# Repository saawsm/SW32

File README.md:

# SW32 - 4 Channel E-Stim

*This project is a work in-progress. Changes to the design might occur. Order PCBs at your own risk..*

---

## About

The SW32 is a 4-channel E-Stim box based around the MK312 box. Focusing on a modern and compact redesign. It supports USB Type-C PD charging with a variety of batteries such as Li-Ion, Li-Poly, or Lead Acid.

Controlling and interacting with the box can be achieved in numerous ways. Such as the front panel controls, USB, Bluetooth/A2DP, or via Wi-Fi using the internally hosted web app.

An RP2040 microcontroller was picked since it has dual cores and the [PIO](https://www.raspberrypi.com/documentation/pico-sdk/hardware.html#rpip27a2111bf36b4a04eb7b) hardware peripheral. An active community and well documented SDK is also a bonus.

## Features

* 1.8" 160x128 Color Display
* 4x Isolated Output Channels
  * Triphase Support
  * Tri-polar (+, GND, -) Support
* Stereo Line-In and Mono Microphone Input (with programmable gain)
* Internal Microphone
* 4x Trigger Channels
* USB Type-C PD Charging
* Multi-chemistry Battery Pack Support (Li-Ion/Li-Poly/Lead Acid)

## Overview

The SW32 consists of following PCBs:

* Main Board - Provides the core functionality of the SW32.
* Output Board - Generates the isolated E-Stim output for each channel. Driven by the main board.
* Front Control Board - The PCB with all the front panel controls (e.g. pots, buttons, LEDs).
* Front Panel - A cosmetic silkscreen PCB for the front control board.
* Display Module* - 1.8" 160x128 TFT SPI color display.

The reason for having a separate output board is primarily for flexibility, space savings (expand vertically instead of horizontally), and long-term cost savings. Most of the cost is in the main board. So being able to reuse the main board when changing the output design will help keep costs down.

## Fabrication

This build is mostly SMT with THT for connectors and front panel components. PCBs have been designed specifically for JLCPCB fabrication and assembly.

Schematics can be found in [/schematics](/schematics), and PCB fabrication files (gerbers, BoMs, CPL, etc.) can be found in [/pcb](/pcb).

## Disclaimer

The SW32 comes with absolutely no warranty of any kind. The designs are free to use, under the conditions defined in the [LICENSE](LICENSE). Using the designs in original or modified form, implies acceptance of any and all associated risks and liabilities.

* Use it entirely at your own risk.
* Do not use it for anything safety-critical, medical, industrial, military, or illegal.
* Do not use it on anyone without explicit and informed consent.
* Keep any and all electrodes below the chest.
* Do not use Li-Ion battery packs without a BMS.

### Safety

SW32 can generate potentially lethal voltages and currents on its outputs and on internal components, even when powered from a battery. The risks associated with building, testing and using this device can be reduced but not eliminated.

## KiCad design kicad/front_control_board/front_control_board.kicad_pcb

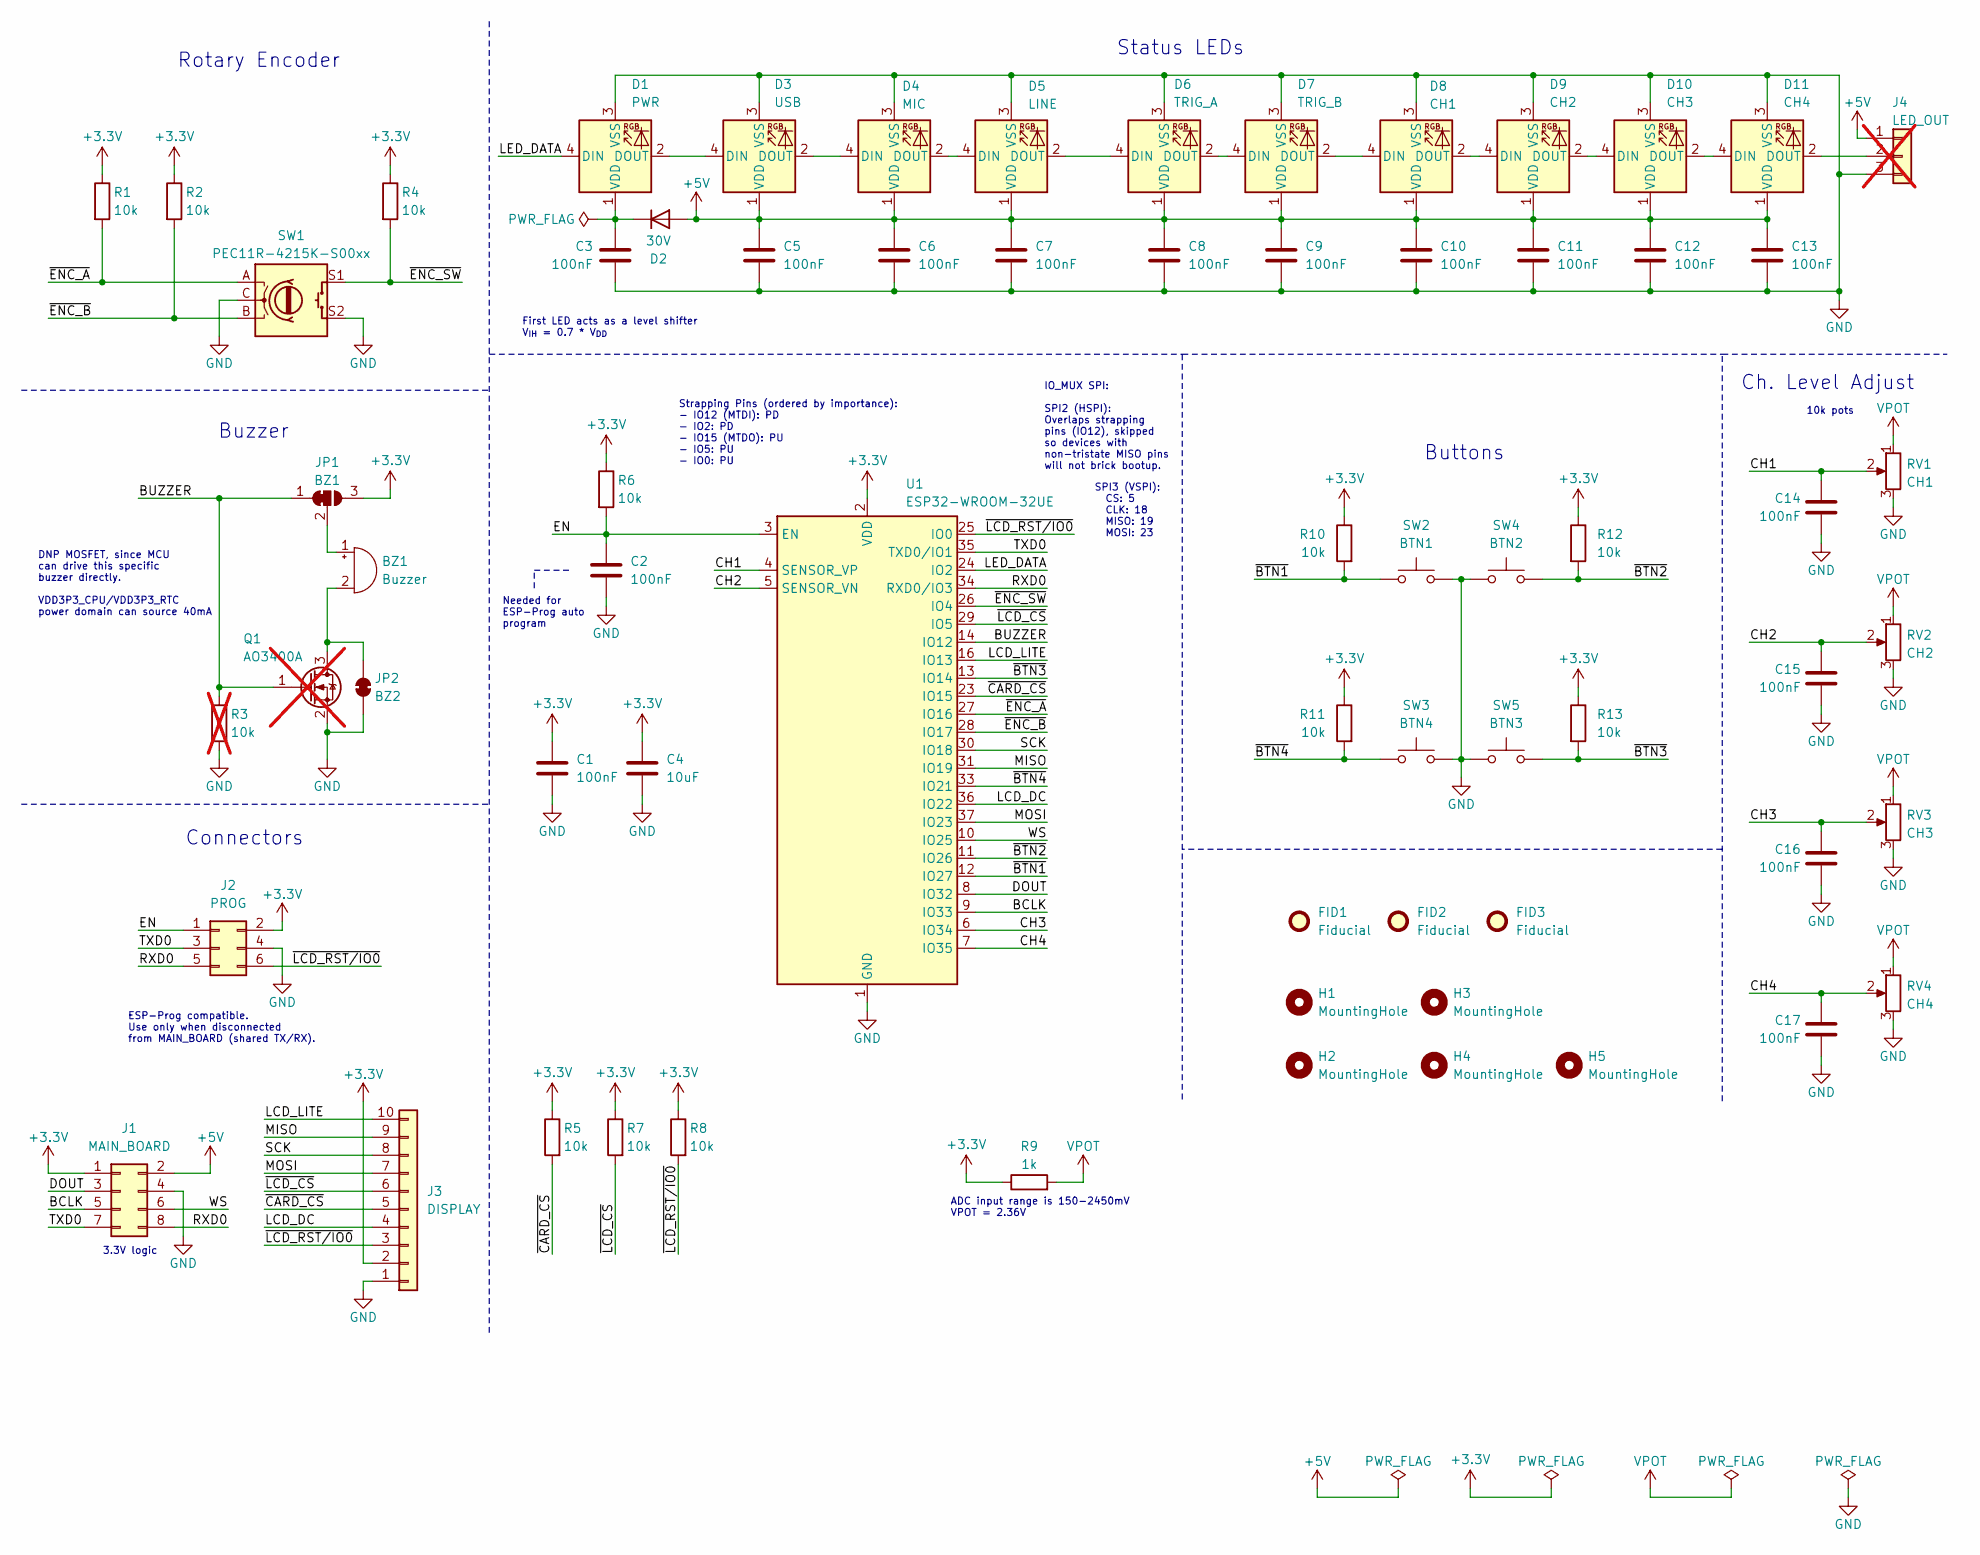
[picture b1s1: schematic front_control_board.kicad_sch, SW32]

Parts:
BZ1: Buzzer; Buzzer_12x9.5RM7.6; LCSC C409834
C1, C2, C3, C5, C6, C7, C8, C9, C10, C11, C12, C13, C14, C15, C16, C17: 100nF; C_0603_1608Metric; LCSC C14663
C4: 10uF; C_0603_1608Metric; LCSC C96446
D1: PWR; LED_WS2812B_PLCC4_5.0x5.0mm_P3.2mm; LCSC C2843785
D2: 30V; D_SOD-323; LCSC C2128
D3: USB; LED_WS2812B_PLCC4_5.0x5.0mm_P3.2mm; LCSC C2843785
D4: MIC; LED_WS2812B_PLCC4_5.0x5.0mm_P3.2mm; LCSC C2843785
D5: LINE; LED_WS2812B_PLCC4_5.0x5.0mm_P3.2mm; LCSC C2843785
D6: TRIG_A; LED_WS2812B_PLCC4_5.0x5.0mm_P3.2mm; LCSC C2843785
D7: TRIG_B; LED_WS2812B_PLCC4_5.0x5.0mm_P3.2mm; LCSC C2843785
D8: CH1; LED_WS2812B_PLCC4_5.0x5.0mm_P3.2mm; LCSC C2843785
D9: CH2; LED_WS2812B_PLCC4_5.0x5.0mm_P3.2mm; LCSC C2843785
D10: CH3; LED_WS2812B_PLCC4_5.0x5.0mm_P3.2mm; LCSC C2843785
D11: CH4; LED_WS2812B_PLCC4_5.0x5.0mm_P3.2mm; LCSC C2843785
FID1, FID2, FID3: Fiducial; Fiducial_1mm_Mask2mm
H1, H2, H3, H4, H5: MountingHole; MountingHole_2.2mm_M2
J1: MAIN_BOARD; IDC-Header_2x04_P2.54mm_Vertical; LCSC C5372864
J2: PROG; IDC-Header_2x03_P2.54mm_Vertical; LCSC C5372863
J3: DISPLAY; PinHeader_1x10_P2.54mm_Vertical; LCSC C492409
J4: LED_OUT; PinHeader_1x03_P2.54mm_Vertical; LCSC C2937625; not fitted
JP1: BZ1; SolderJumper-3_P1.3mm_Bridged12_RoundedPad1.0x1.5mm_NumberL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
JP2: BZ2; SolderJumper-2_P1.3mm_Bridged_RoundedPad1.0x1.5mm
Q1: AO3400A; SOT-23; LCSC C20917; not fitted
R1, R2, R4, R5, R6, R7, R8, R10, R11, R12, R13: 10k; R_0603_1608Metric; LCSC C25804
R3: 10k; R_0603_1608Metric; LCSC C25804; not fitted
R9: 1k; R_0603_1608Metric; LCSC C21190
RV1: CH1; Potentiometer_Bourns_PTV09A-1_Single_Vertical; LCSC C6149573
RV2: CH2; Potentiometer_Bourns_PTV09A-1_Single_Vertical; LCSC C6149573
RV3: CH3; Potentiometer_Bourns_PTV09A-1_Single_Vertical; LCSC C6149573
RV4: CH4; Potentiometer_Bourns_PTV09A-1_Single_Vertical; LCSC C6149573
SW1: PEC11R-4215K-S00xx; Rotary_Encoder_Switched_PEC11R; LCSC C7275025
SW2: BTN1; SW_PUSH_6mm_H5mm; LCSC C393938
SW3: BTN4; SW_PUSH_6mm_H5mm; LCSC C393938
SW4: BTN2; SW_PUSH_6mm_H5mm; LCSC C393938
SW5: BTN3; SW_PUSH_6mm_H5mm; LCSC C393938
U1: ESP32-WROOM-32UE; LCSC C701346

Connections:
+3.3V: C1.1, C4.1, J1.1, J2.2, J3.2, JP1.3 (B), R1.1, R2.1, R4.1, R5.1, R6.1, R7.1, R8.1, R9.1, R10.1, R11.1, R12.1, R13.1, U1.2 (VDD)
+5V: C5.1, C6.1, C7.1, C8.1, C9.1, C10.1, C11.1, C12.1, C13.1, D2.2 (A), D3.1 (VDD), D4.1 (VDD), D5.1 (VDD), D6.1 (VDD), D7.1 (VDD), D8.1 (VDD), D9.1 (VDD), D10.1 (VDD), D11.1 (VDD), J1.2, J4.1
/BCLK: J1.5, U1.9 (IO33)
/BUZZER: JP1.1 (A), Q1.1 (G), R3.2, U1.14 (IO12)
/CH1: C14.1, RV1.2, U1.4 (SENSOR_VP)
/CH2: C15.1, RV2.2, U1.5 (SENSOR_VN)
/CH3: C16.1, RV3.2, U1.6 (IO34)
/CH4: C17.1, RV4.2, U1.7 (IO35)
/DOUT: J1.3, U1.8 (IO32)
/EN: C2.1, J2.1, R6.2, U1.3 (EN)
/LCD_DC: J3.4, U1.36 (IO22)
/LCD_LITE: J3.10, U1.16 (IO13)
/LED_DATA: D1.4 (DIN), U1.24 (IO2)
/MISO: J3.9, U1.31 (IO19)
/MOSI: J3.7, U1.37 (IO23)
/RXD0: J1.8, J2.5, U1.34 (RXD0/IO3)
/SCK: J3.8, U1.30 (IO18)
/TXD0: J1.7, J2.3, U1.35 (TXD0/IO1)
/WS: J1.6, U1.10 (IO25)
/~BTN1: R10.2, SW2.2, U1.12 (IO27)
/~BTN2: R12.2, SW4.2, U1.11 (IO26)
/~BTN3: R13.2, SW5.2, U1.13 (IO14)
/~BTN4: R11.2, SW3.2, U1.33 (IO21)
/~CARD_CS: J3.5, R5.2, U1.23 (IO15)
/~ENC_A: R1.2, SW1.A, U1.27 (IO16)
/~ENC_B: R2.2, SW1.B, U1.28 (IO17)
/~ENC_SW: R4.2, SW1.S1, U1.26 (IO4)
/~LCD_CS: J3.6, R7.2, U1.29 (IO5)
/~LCD_RST/IO0: J2.6, J3.3, R8.2, U1.25 (IO0)
GND: C1.2, C2.2, C3.2, C4.2, C5.2, C6.2, C7.2, C8.2, C9.2, C10.2, C11.2, C12.2, C13.2, C14.2, C15.2, C16.2, C17.2, D1.3 (VSS), D3.3 (VSS), D4.3 (VSS), D5.3 (VSS), D6.3 (VSS), D7.3 (VSS), D8.3 (VSS), D9.3 (VSS), D10.3 (VSS), D11.3 (VSS), J1.4, J2.4, J3.1, J4.3, JP2.1 (A), Q1.2 (S), R3.1, RV1.3, RV2.3, RV3.3, RV4.3, SW1.C, SW1.S2, SW2.1, SW3.1, SW4.1, SW5.1, U1.1 (GND), U1.15 (GND), U1.38 (GND), U1.39 (GND)
unnamed: BZ1.1 (+), JP1.2 (C)
unnamed: BZ1.2 (-), JP2.2 (B), Q1.3 (D)
unnamed: D1.2 (DOUT), D3.4 (DIN)
unnamed: C3.1, D1.1 (VDD), D2.1 (K)
unnamed: D3.2 (DOUT), D4.4 (DIN)
unnamed: D4.2 (DOUT), D5.4 (DIN)
unnamed: D5.2 (DOUT), D6.4 (DIN)
unnamed: D6.2 (DOUT), D7.4 (DIN)
unnamed: D7.2 (DOUT), D8.4 (DIN)
unnamed: D8.2 (DOUT), D9.4 (DIN)
unnamed: D9.2 (DOUT), D10.4 (DIN)
unnamed: D10.2 (DOUT), D11.4 (DIN)
unnamed: D11.2 (DOUT), J4.2
VPOT: R9.2, RV1.1, RV2.1, RV3.1, RV4.1

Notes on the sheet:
Status LEDs
ADC input range is 150-2450mV VPOT = 2.36V
First LED acts as a level shifter V_{IH} = 0.7 * V_{DD}
Rotary Encoder
IO_MUX SPI: SPI2 (HSPI): Overlaps strapping pins (IO12), skipped so devices with non-tristate MISO pins will not brick bootup.
SPI3 (VSPI): CS: 5 CLK: 18 MISO: 19 MOSI: 23
Buttons
3.3V logic
ESP-Prog compatible. Use only when disconnected from MAIN_BOARD (shared TX/RX).
Strapping Pins (ordered by importance): - IO12 (MTDI): PD - IO2: PD - IO15 (MTDO): PU - IO5: PU - IO0: PU
Connectors
10k pots
Needed for ESP-Prog auto program
Buzzer
DNP MOSFET, since MCU can drive this specific buzzer directly. VDD3P3_CPU/VDD3P3_RTC power domain can source 40mA
Ch. Level Adjust

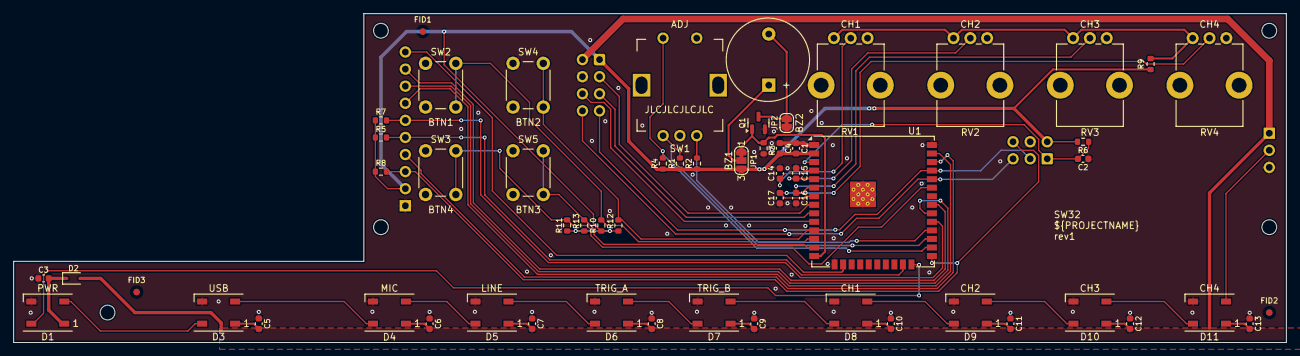
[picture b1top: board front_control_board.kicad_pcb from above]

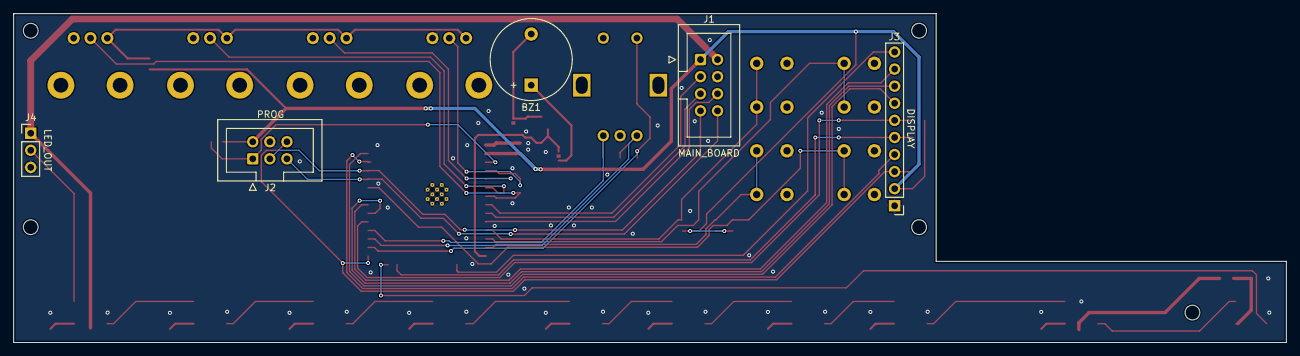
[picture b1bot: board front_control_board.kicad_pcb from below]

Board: 2 copper layers, 189.2 x 48.9 mm, 67 parts (5 on the bottom side), 44 nets.

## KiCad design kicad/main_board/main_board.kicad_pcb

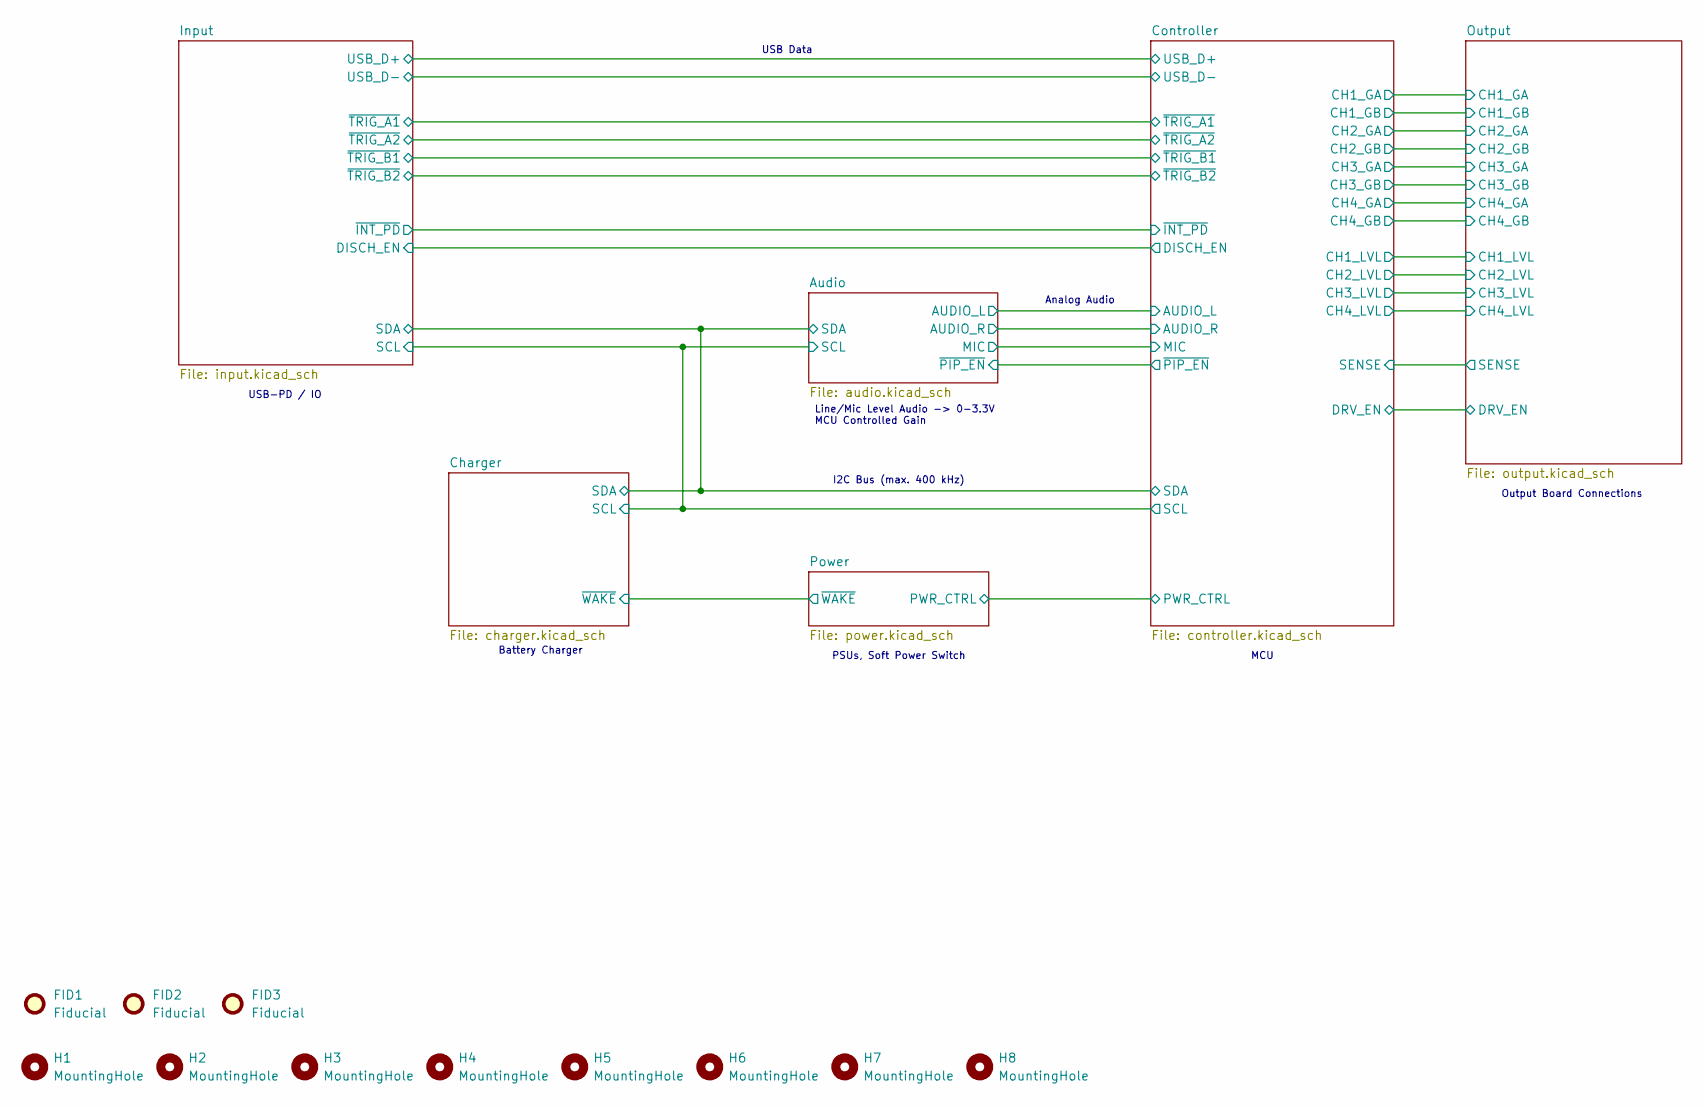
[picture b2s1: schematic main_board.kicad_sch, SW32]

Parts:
FID1, FID2, FID3: Fiducial; Fiducial_1mm_Mask2mm
H1, H2, H3, H4, H5, H6, H7, H8: MountingHole; MountingHole_2.2mm_M2

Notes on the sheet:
Output Board Connections
USB-PD / IO
MCU
USB Data
PSUs, Soft Power Switch
Line/Mic Level Audio -> 0-3.3V MCU Controlled Gain
Analog Audio
Battery Charger
I2C Bus (max. 400 kHz)

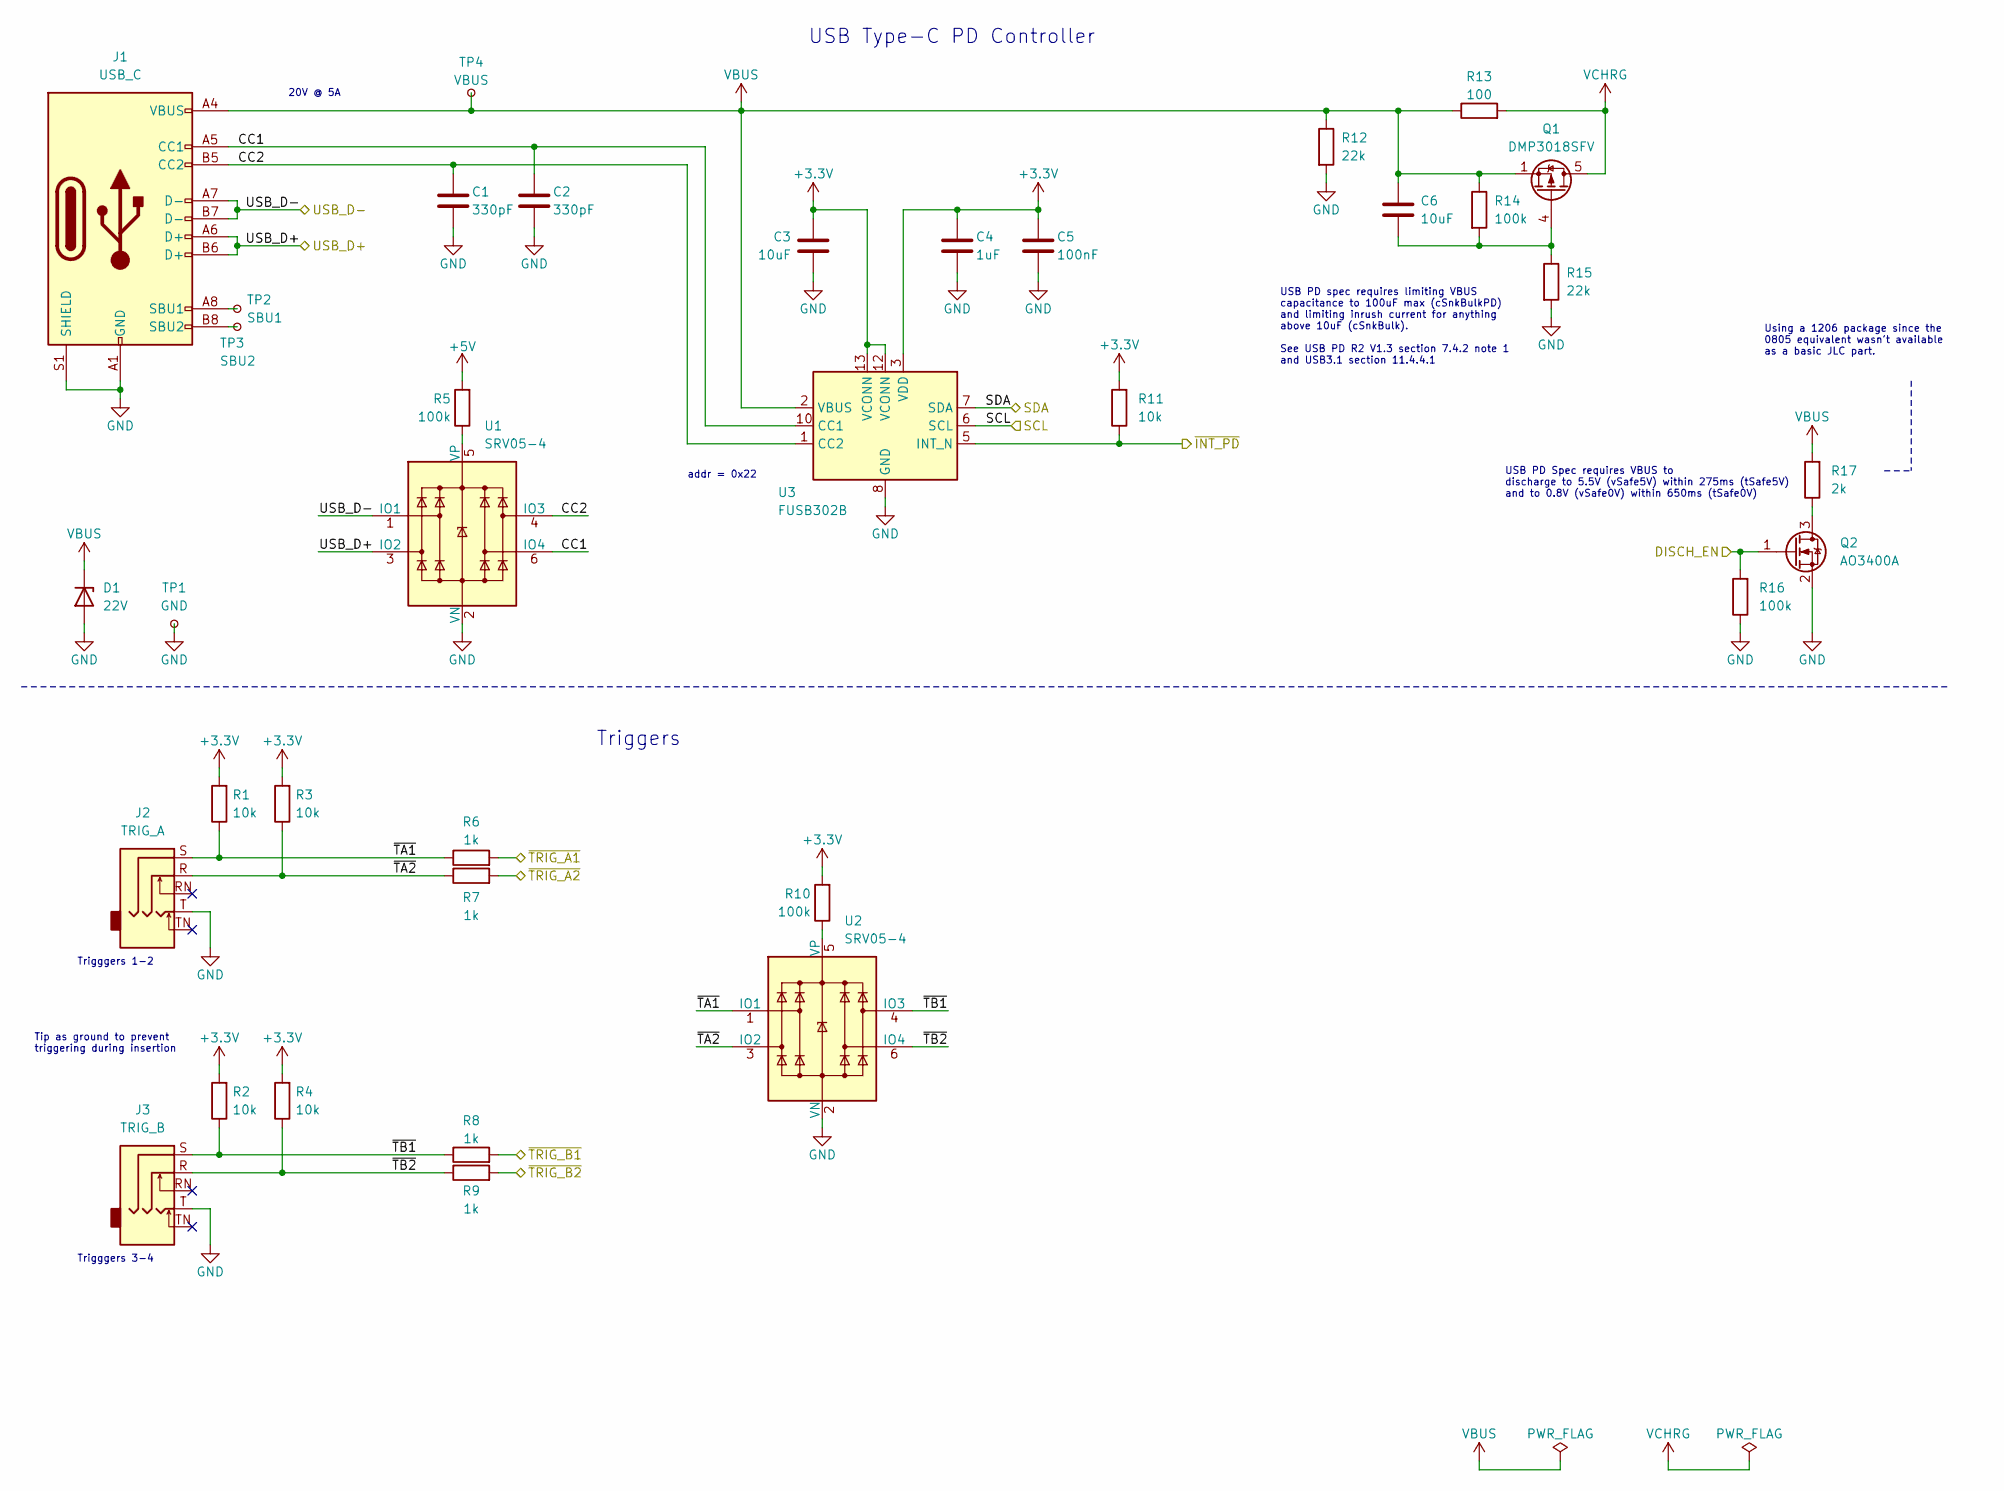
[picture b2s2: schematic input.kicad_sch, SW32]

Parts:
C1, C2: 330pF; C_0603_1608Metric; LCSC C1664
C3, C6: 10uF; C_0603_1608Metric; LCSC C96446
C4: 1uF; C_0603_1608Metric; LCSC C15849
C5: 100nF; C_0603_1608Metric; LCSC C14663
D1: 22V; ST_QFN-2L_1.6x1.0mm; LCSC C1974707
J1: USB_C; USB_C_Receptacle_GCT_USB4105-xx-A_16P_TopMnt_Horizontal; LCSC C2765186
J2: TRIG_A; PJ-3062-CO; LCSC C319113
J3: TRIG_B; PJ-3062-CO; LCSC C319113
Q1: DMP3018SFV; Diodes_PowerDI3333-8_ThermalVias; LCSC C461075
Q2: AO3400A; SOT-23; LCSC C20917
R1, R2, R3, R4, R11: 10k; R_0603_1608Metric; LCSC C25804
R5, R10, R14, R16: 100k; R_0603_1608Metric; LCSC C25803
R6, R7, R8, R9: 1k; R_0603_1608Metric; LCSC C21190
R12, R15: 22k; R_0603_1608Metric; LCSC C31850
R13: 100; R_1206_3216Metric; LCSC C17901
R17: 2k; R_1206_3216Metric; LCSC C17944
TP1: GND; TestPoint_Pad_D1.0mm
TP2: SBU1; TestPoint_Pad_D1.0mm
TP3: SBU2; TestPoint_Pad_D1.0mm
TP4: VBUS; TestPoint_Pad_D1.0mm
U1, U2: SRV05-4; SOT-23-6; LCSC C111212
U3: FUSB302B; WQFN-14-1EP_2.5x2.5mm_P0.5mm_EP1.45x1.45mm; LCSC C132291

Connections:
+3.3V: C3.1, C4.1, C5.1, R1.2, R2.2, R3.2, R4.2, R10.2, R11.2, U3.3 (VDD), U3.4 (VDD), U3.12 (VCONN), U3.13 (VCONN); also elsewhere on the board
+5V: R5.2; also elsewhere on the board
/Charger/SCL: U3.6 (SCL); also elsewhere on the board
/Charger/SDA: U3.7 (SDA); also elsewhere on the board
/Controller/DISCH_EN: Q2.1 (G), R16.2; also elsewhere on the board
/Controller/~INT_PD: R11.1, U3.5 (INT_N); also elsewhere on the board
/Controller/~TRIG_A1: R6.2; also elsewhere on the board
/Controller/~TRIG_A2: R7.2; also elsewhere on the board
/Controller/~TRIG_B1: R8.2; also elsewhere on the board
/Controller/~TRIG_B2: R9.2; also elsewhere on the board
/Input/CC1: C2.1, J1.A5 (CC1), U1.6 (IO4), U3.10 (CC1), U3.11 (CC1)
/Input/CC2: C1.1, J1.B5 (CC2), U1.4 (IO3), U3.1 (CC2), U3.14 (CC2)
/Input/USB_D+: J1.A6 (D+), J1.B6 (D+), U1.3 (IO2); also elsewhere on the board
/Input/USB_D-: J1.A7 (D-), J1.B7 (D-), U1.1 (IO1); also elsewhere on the board
/Input/~TA1: J2.S, R1.1, R6.1, U2.1 (IO1)
/Input/~TA2: J2.R, R3.1, R7.1, U2.3 (IO2)
/Input/~TB1: J3.S, R2.1, R8.1, U2.4 (IO3)
/Input/~TB2: J3.R, R4.1, R9.1, U2.6 (IO4)
GND: C1.2, C2.2, C3.2, C4.2, C5.2, D1.2 (A), J1.A1 (GND), J1.A12 (GND), J1.B1 (GND), J1.B12 (GND), J1.S1 (SHIELD), J2.T, J3.T, Q2.2 (S), R12.2, R15.2, R16.1, TP1.1, U1.2 (VN), U2.2 (VN), U3.8 (GND), U3.9 (GND), U3.15 (GND); also elsewhere on the board
unnamed: J1.A8 (SBU1), TP2.1
unnamed: J1.B8 (SBU2), TP3.1
unnamed: C6.2, Q1.4 (G), R14.2, R15.1
unnamed: Q2.3 (D), R17.1
unnamed: R5.1, U1.5 (VP)
unnamed: R10.1, U2.5 (VP)
VBUS: C6.1, D1.1 (K), J1.A4 (VBUS), J1.A9 (VBUS), J1.B4 (VBUS), J1.B9 (VBUS), Q1.1 (S), Q1.2 (S), Q1.3 (S), R12.1, R13.1, R14.1, R17.2, TP4.1, U3.2 (VBUS); also elsewhere on the board
VCHRG: Q1.5 (D), R13.2; also elsewhere on the board

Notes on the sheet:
USB Type-C PD Controller
Triggers
Trigggers 3-4
20V @ 5A
USB PD spec requires limiting VBUS capacitance to 100uF max (cSnkBulkPD) and limiting inrush current for anything above 10uF (cSnkBulk). See USB PD R2 V1.3 section 7.4.2 note 1 and USB3.1 section 11.4.4.1
Tip as ground to prevent triggering during insertion
Using a 1206 package since the 0805 equivalent wasn't available as a basic JLC part.
USB PD Spec requires VBUS to discharge to 5.5V (vSafe5V) within 275ms (tSafe5V) and to 0.8V (vSafe0V) within 650ms (tSafe0V)
addr = 0x22
Trigggers 1-2

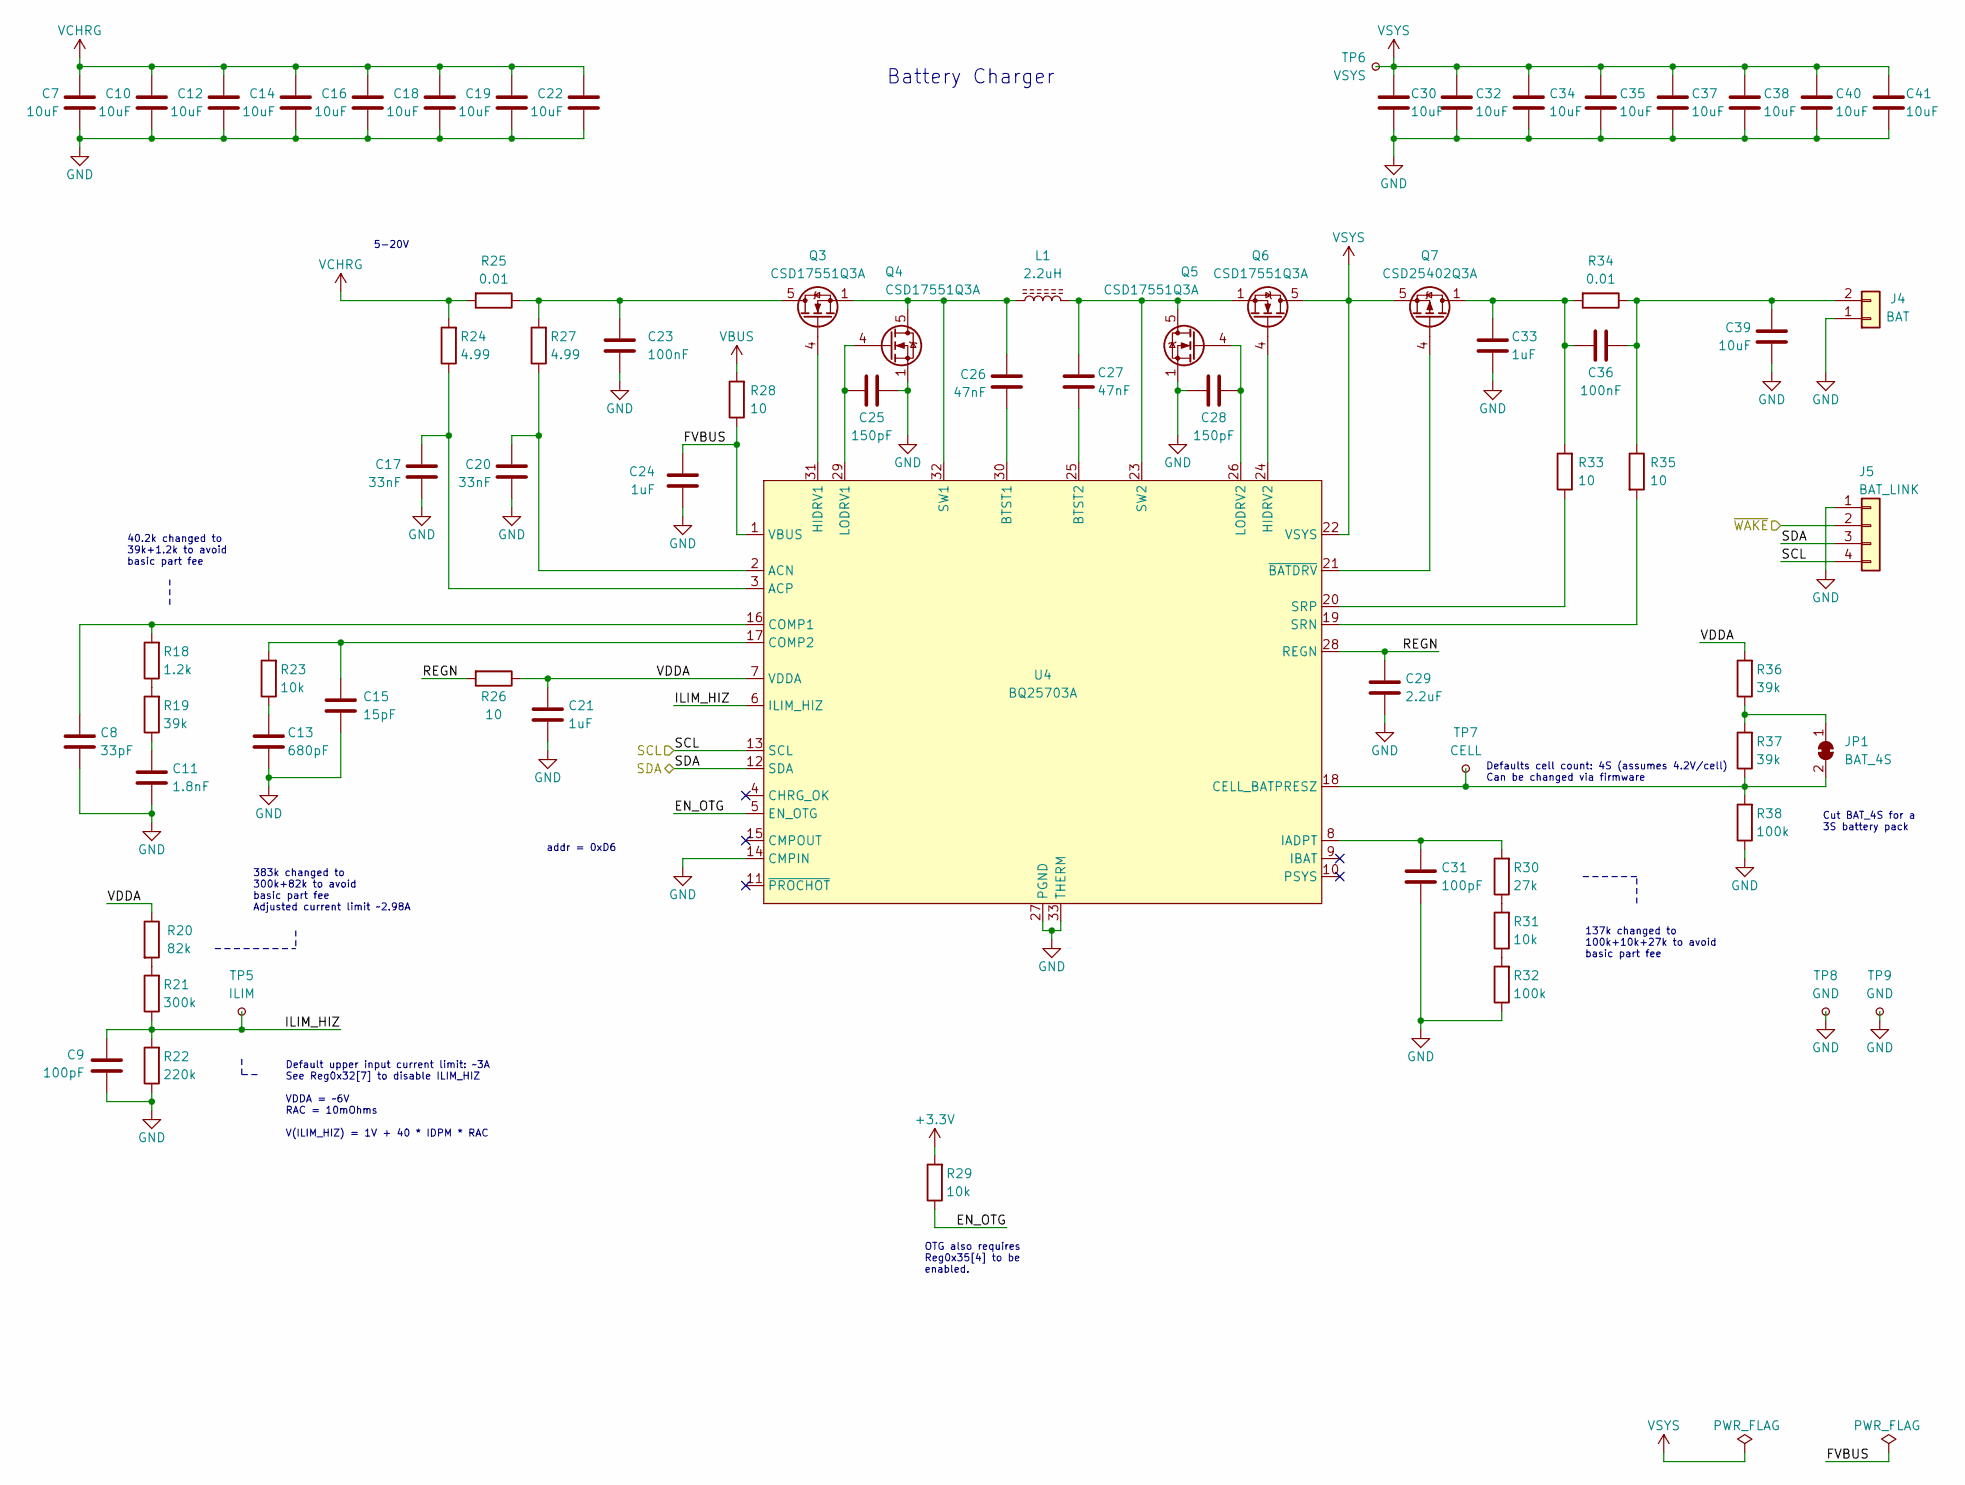
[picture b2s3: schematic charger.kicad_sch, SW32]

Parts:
C7, C10, C12, C14, C16, C18, C19, C22, C30, C32, C34, C35, C37, C38, C39, C40, C41: 10uF; C_0805_2012Metric; LCSC C440198
C8: 33pF; C_0603_1608Metric; LCSC C1663
C9, C31: 100pF; C_0603_1608Metric; LCSC C14858
C11: 1.8nF; C_0603_1608Metric; LCSC C318642
C13: 680pF; C_0603_1608Metric; LCSC C30816
C15: 15pF; C_0603_1608Metric; LCSC C1644
C17, C20: 33nF; C_0603_1608Metric; LCSC C21117
C21, C24, C33: 1uF; C_0603_1608Metric; LCSC C15849
C23, C36: 100nF; C_0603_1608Metric; LCSC C14663
C25, C28: 150pF; C_0603_1608Metric; LCSC C37298
C26, C27: 47nF; C_0603_1608Metric; LCSC C1622
C29: 2.2uF; C_0603_1608Metric; LCSC C23630
J4: BAT; AMASS_XT30UPB-M_1x02_P5.0mm_Vertical; LCSC C428721
J5: BAT_LINK; JST_XH_B4B-XH-A_1x04_P2.50mm_Vertical; LCSC C7429634
JP1: BAT_4S; SolderJumper-2_P1.3mm_Bridged_RoundedPad1.0x1.5mm
L1: 2.2uH; L_Vishay_IHLP-2525; LCSC C540967
Q3, Q4, Q5, Q6: CSD17551Q3A; VSON-8_3.3x3.3mm_P0.65mm_NexFET_ThermalVias; LCSC C2876535
Q7: CSD25402Q3A; VSON-8_3.3x3.3mm_P0.65mm_NexFET_ThermalVias; LCSC C111356
R18: 1.2k; R_0603_1608Metric; LCSC C22765
R19, R36, R37: 39k; R_0603_1608Metric; LCSC C23153
R20: 82k; R_0603_1608Metric; LCSC C23254
R21: 300k; R_0603_1608Metric; LCSC C23024
R22: 220k; R_0603_1608Metric; LCSC C22961
R23, R29, R31: 10k; R_0603_1608Metric; LCSC C25804
R24, R27: 4.99; R_0603_1608Metric; LCSC C137704
R25, R34: 0.01; R_1206_3216Metric; LCSC C844910
R26, R28, R33, R35: 10; R_0603_1608Metric; LCSC C22859
R30: 27k; R_0603_1608Metric; LCSC C22967
R32, R38: 100k; R_0603_1608Metric; LCSC C25803
TP5: ILIM; TestPoint_Pad_D1.0mm
TP6: VSYS; TestPoint_Pad_D1.0mm
TP7: CELL; TestPoint_Pad_D1.0mm
TP8, TP9: GND; TestPoint_Pad_D1.0mm
U4: BQ25703A; Texas_S-PWQFN-N32_EP2.8x2.8mm_ThermalVias; LCSC C188229

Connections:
+3.3V: R29.2; also elsewhere on the board
/Charger/EN_OTG: R29.1, U4.5 (EN_OTG)
/Charger/FVBUS: C24.1, R28.1, U4.1 (VBUS)
/Charger/ILIM_HIZ: C9.1, R21.1, R22.2, TP5.1, U4.6 (ILIM_HIZ)
/Charger/REGN: C29.1, R26.2, U4.28 (REGN)
/Charger/SCL: J5.4, U4.13 (SCL); also elsewhere on the board
/Charger/SDA: J5.3, U4.12 (SDA); also elsewhere on the board
/Charger/VDDA: C21.1, R20.1, R26.1, R36.2, U4.7 (VDDA)
/Charger/~WAKE: J5.2; also elsewhere on the board
GND: C7.2, C8.2, C9.2, C10.2, C11.2, C12.2, C13.2, C14.2, C15.2, C16.2, C17.1, C18.2, C19.2, C20.1, C21.2, C22.2, C23.1, C24.2, C25.2, C28.1, C29.2, C30.2, C31.2, C32.2, C33.2, C34.2, C35.2, C37.2, C38.2, C39.2, C40.2, C41.2, J4.1, J5.1, Q4.1 (S), Q4.2 (S), Q4.3 (S), Q5.1 (S), Q5.2 (S), Q5.3 (S), R22.1, R32.1, R38.1, TP8.1, TP9.1, U4.14 (CMPIN), U4.27 (PGND), U4.33 (THERM); also elsewhere on the board
unnamed: C11.1, R19.1
unnamed: C13.1, R23.1
unnamed: C33.1, C36.1, Q7.1 (D), Q7.2 (D), Q7.3 (D), R33.2, R34.2
unnamed: C36.2, C39.1, J4.2, R34.1, R35.1
unnamed: JP1.1 (A), R36.1, R37.2
unnamed: JP1.2 (B), R37.1, R38.2, TP7.1, U4.18 (CELL_BATPRESZ)
unnamed: C23.2, Q3.5 (D), R25.1, R27.2
unnamed: Q3.4 (G), U4.31 (HIDRV1)
unnamed: C26.2, L1.1, Q3.1 (S), Q3.2 (S), Q3.3 (S), Q4.5 (D), U4.32 (SW1)
unnamed: C25.1, Q4.4 (G), U4.29 (LODRV1)
unnamed: C27.2, L1.2, Q5.5 (D), Q6.1 (S), Q6.2 (S), Q6.3 (S), U4.23 (SW2)
unnamed: C28.2, Q5.4 (G), U4.26 (LODRV2)
unnamed: Q6.4 (G), U4.24 (HIDRV2)
unnamed: Q7.4 (G), U4.21 (~BATDRV)
unnamed: R18.1, R19.2
unnamed: R20.2, R21.2
unnamed: R30.1, R31.2
unnamed: R31.1, R32.2
unnamed: C20.2, R27.1, U4.2 (ACN)
unnamed: C17.2, R24.1, U4.3 (ACP)
unnamed: C26.1, U4.30 (BTST1)
unnamed: C27.1, U4.25 (BTST2)
unnamed: C8.1, R18.2, U4.16 (COMP1)
unnamed: C15.1, R23.2, U4.17 (COMP2)
unnamed: C31.1, R30.2, U4.8 (IADPT)
unnamed: R35.2, U4.19 (SRN)
unnamed: R33.1, U4.20 (SRP)
VBUS: R28.2; also elsewhere on the board
VCHRG: C7.1, C10.1, C12.1, C14.1, C16.1, C18.1, C19.1, C22.1, R24.2, R25.2; also elsewhere on the board
VSYS: C30.1, C32.1, C34.1, C35.1, C37.1, C38.1, C40.1, C41.1, Q6.5 (D), Q7.5 (S), TP6.1, U4.22 (VSYS); also elsewhere on the board

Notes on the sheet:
383k changed to 300k+82k to avoid basic part fee Adjusted current limit ~2.98A
40.2k changed to 39k+1.2k to avoid basic part fee
addr = 0xD6
Defaults cell count: 4S (assumes 4.2V/cell) Can be changed via firmware
Cut BAT_4S for a 3S battery pack
Default upper input current limit: ~3A See Reg0x32[7] to disable ILIM_HIZ VDDA = ~6V RAC = 10mOhms V(ILIM_HIZ) = 1V + 40 * IDPM * RAC
5-20V
137k changed to 100k+10k+27k to avoid basic part fee
OTG also requires Reg0x35[4] to be enabled.
Battery Charger

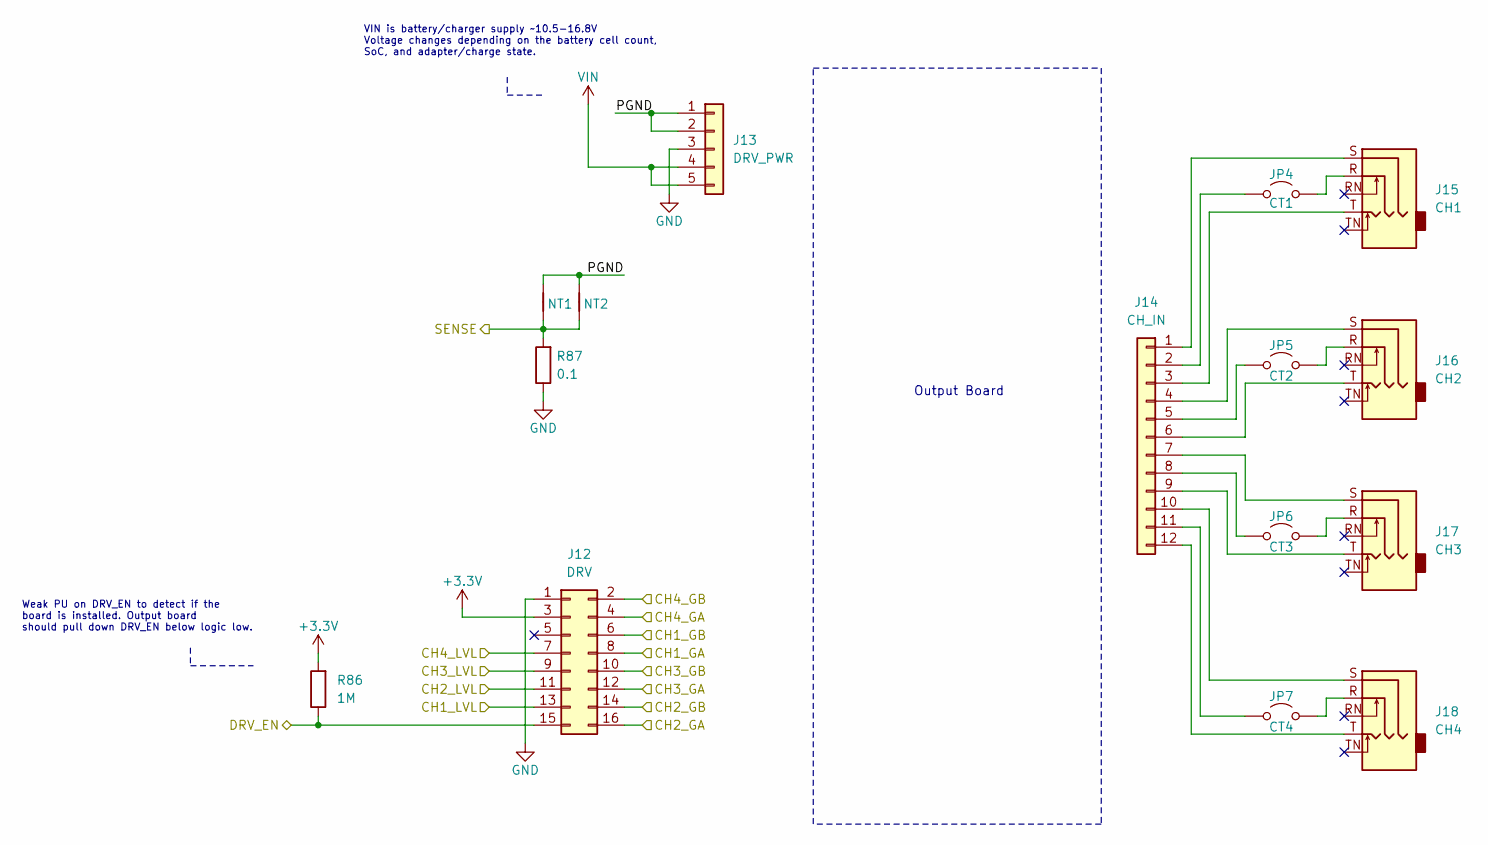
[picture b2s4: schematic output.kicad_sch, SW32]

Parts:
J12: DRV; PinSocket_2x08_P2.54mm_Vertical; LCSC C2897409
J13: DRV_PWR; PinSocket_1x05_P2.54mm_Vertical; LCSC C2897368
J14: CH_IN; PinHeader_1x12_P2.54mm_Vertical; LCSC C2840012
J15: CH1; PJ-3062-CO; LCSC C319113
J16: CH2; PJ-3062-CO; LCSC C319113
J17: CH3; PJ-3062-CO; LCSC C319113
J18: CH4; PJ-3062-CO; LCSC C319113
JP4: CT1; PinHeader_1x02_P2.54mm_Vertical; LCSC C492401
JP5: CT2; PinHeader_1x02_P2.54mm_Vertical; LCSC C492401
JP6: CT3; PinHeader_1x02_P2.54mm_Vertical; LCSC C492401
JP7: CT4; PinHeader_1x02_P2.54mm_Vertical; LCSC C492401
NT1, NT2: NetTie-2_SMD_Pad2.0mm
R86: 1M; R_0603_1608Metric; LCSC C22935
R87: 0.1; R_2512_6332Metric; LCSC C165698

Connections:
+3.3V: J12.3, R86.2; also elsewhere on the board
/Controller/CH1_GA: J12.8; also elsewhere on the board
/Controller/CH1_GB: J12.6; also elsewhere on the board
/Controller/CH1_LVL: J12.13; also elsewhere on the board
/Controller/CH2_GA: J12.16; also elsewhere on the board
/Controller/CH2_GB: J12.14; also elsewhere on the board
/Controller/CH2_LVL: J12.11; also elsewhere on the board
/Controller/CH3_GA: J12.12; also elsewhere on the board
/Controller/CH3_GB: J12.10; also elsewhere on the board
/Controller/CH3_LVL: J12.9; also elsewhere on the board
/Controller/CH4_GA: J12.4; also elsewhere on the board
/Controller/CH4_GB: J12.2; also elsewhere on the board
/Controller/CH4_LVL: J12.7; also elsewhere on the board
/Controller/DRV_EN: J12.15, R86.1; also elsewhere on the board
/Controller/SENSE: NT1.1, NT2.1, R87.2; also elsewhere on the board
/Output/PGND: J13.1, J13.2, NT1.2, NT2.2
GND: J12.1, J13.3, R87.1; also elsewhere on the board
unnamed: J14.1, J15.S
unnamed: J14.2, JP4.1 (A)
unnamed: J14.3, J15.T
unnamed: J14.4, J16.S
unnamed: J14.5, JP5.1 (A)
unnamed: J14.6, J16.T
unnamed: J14.7, J17.S
unnamed: J14.8, JP6.1 (A)
unnamed: J14.9, J17.T
unnamed: J14.10, J18.S
unnamed: J14.11, JP7.1 (A)
unnamed: J14.12, J18.T
unnamed: J15.R, JP4.2 (B)
unnamed: J16.R, JP5.2 (B)
unnamed: J17.R, JP6.2 (B)
unnamed: J18.R, JP7.2 (B)
VIN: J13.4, J13.5; also elsewhere on the board

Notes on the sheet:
VIN is battery/charger supply ~10.5-16.8V Voltage changes depending on the battery cell count, SoC, and adapter/charge state.
Output Board
Weak PU on DRV_EN to detect if the board is installed. Output board should pull down DRV_EN below logic low.
